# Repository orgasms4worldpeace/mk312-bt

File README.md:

# MK-312BT

DIY build of the **ErosTek ET-312B** e-stim power box, with Bluetooth (HC-05) or WiFi (ESP8266) wireless control. Boards, BOM, firmware, case, and the documentation needed to actually build one.

> ⚠️ **Safety.** This is a high-voltage device. Don't injure yourself. No warranty.

## How to build one

Work through the numbered directories in order. The full step-by-step walkthrough is in **[`build-guide.md`](build-guide.md)**.

| Step | Directory | What you do |
|------|-----------|-------------|
| 1 | [`1-order-boards/`](1-order-boards/) | Send the main-board + front-panel gerbers to JLCPCB |
| 2 | [`2-order-parts/`](2-order-parts/) | Import the BOM into Mouser. Pre-match MOSFETs by Vt — this prevents Error 20 |
| 3 | [`3-build-and-flash/`](3-build-and-flash/) | Solder, print the case, flash the ATmega16A |
| 4 | [`4-wireless/`](4-wireless/) | Pick **Bluetooth** (HC-05) or **WiFi** (ESP8266 — required for macOS / iOS) |
| 5 | [`5-software/`](5-software/) | Pick a control client (links to upstream projects — none bundled) |

If anything misbehaves, [`3-build-and-flash/troubleshooting/`](3-build-and-flash/troubleshooting/) has per-failure-code analyses and the archived metafetish.club forum threads.

## Speculative work in progress

See [`Roadmap.md`](Roadmap.md) for hardware/firmware ideas that haven't been verified end-to-end yet. Nothing in there is on the build path until it lands in the numbered directories.

## What this repo is (and isn't)

A 2026 reorganization of two dormant upstream projects into one build-journey monorepo. Scope: **boards, BOM, firmware, case, build instructions**. Control software stays upstream where it's maintained.

- Upstream for the box: [CrashOverride85/mk312-bt](https://github.com/CrashOverride85/mk312-bt) — boards, firmware, case
- Upstream for the WiFi adapter: [Rangarig/MK312WIFI](https://github.com/Rangarig/MK312WIFI) — pulled into [`4-wireless/wifi/`](4-wireless/wifi/) as a `git subtree`
- Control clients (`mk312-gui`, `ErosWeb`, `three-twelve-bee`, `restim`, etc.): index at [`5-software/`](5-software/) — install whichever from its own repo

This repo is **not** a fork claiming originality, **not** the "official" MK-312BT (there is no official), and **not** a maintained software hub. It's a curation effort with attribution preserved.

### Hardware lineage

```
ErosTek ET-312B               commercial e-stim box (early 2000s, still sold)
└─ metafetish/mk312-bt        community DIY clone, repo deleted ~Dec 2020
   └─ CrashOverride85/mk312-bt   preservation fork, current upstream
      └─ this repo                  2026 reorganization
```

v1.4 board files were DM'd to CrashOverride85 shortly after the metafetish repo was deleted, with no original Eagle source. The design has been built successfully by several people. v1.2 / v1.3 boards (with Eagle source) live in the upstream `CrashOverride85/mk312-bt` repo for anyone who wants to modify the design. Longer story in [`build-guide.md`](build-guide.md#provenance).

### Forum archive

The `metafetish.club` forum — where most community debugging knowledge accumulated — is now offline. Threads on building, Error 20, parts substitution, and firmware live as PDFs in [`3-build-and-flash/troubleshooting/`](3-build-and-flash/troubleshooting/).

## Credit

| Person / project | What they did |
|---|---|
| **CrashOverride85** | Preserved the metafetish repo; ongoing upstream for the box |
| **Rangarig** & **cLx** | MK312WIFI design, schematics, ESP firmware |
| **timduru** | Additional MK312WIFI code contributions |
| **kinkytofu** | [`buttshock-py`](https://github.com/kinkytofu/buttshock-py) — original ET-312 serial-protocol library, predecessor of every Python client |
| **clxjaguar** (cLx) | [`mk312-gui`](https://github.com/clxjaguar/mk312-gui) PyQt client, `mk312-raw-control` |
| **fenbyfluid** | [`three-twelve-bee`](https://github.com/fenbyfluid/three-twelve-bee) web client |
| **boyinsea** | [`ErosWeb`](https://github.com/boyinsea/ErosWeb) sub/dom remote-play client |
| **diglet48** | [`restim`](https://github.com/diglet48/restim) audio-input signal generator |
| **Rubberfate** | [`mk312com`](https://github.com/Rubberfate/mk312com) Python wrapper |
| **Carumbad** | Home Assistant + MQTT bridges |
| **The metafetish.club community** | Board iteration + decades of debug knowledge sitting in the archived threads |
| **ErosTek** | Designers of the ET-312B that this clones |

License: each upstream's original license carries over. New connective material in this repo (READMEs, `build-guide.md`, BOM tooling) is offered freely.

## Getting help

The active community lives in the `#boxes-pulse-based-diy` and `#312-chat` channels on [Joanne's E-Stim Community Discord](https://discord.gg/rY8C27S).

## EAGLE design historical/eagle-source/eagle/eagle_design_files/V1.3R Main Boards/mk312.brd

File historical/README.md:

# Historical artifacts

**Don't build from this folder.** Go back to [the root README](../README.md) and follow the numbered directories.

This folder preserves earlier MK-312BT board revisions and their source artifacts. Kept around because:

- Some builders still work from v1.2 / v1.3 boards they ordered years ago
- The Eagle source (`.brd` / `.sch`) lives here — v1.4 ships gerbers only, so to **modify** the design, start from the v1.3 source
- The build photos in [`images/`](images/) make a useful visual sanity check when assembling

## Contents

| | |
|--|--|
| [`boms/`](boms/) | Original Mouser BOM CSVs and the OpenOffice / Excel masters from the upstream repo |
| [`eagle-source/`](eagle-source/) | Eagle CAD source for v1.2 main board, v1.2 front panel, v1.3B and v1.3R main boards. Includes the Seeed Gerber generator CAM job |
| [`gerbers/`](gerbers/) | Output gerbers for v1.2 main board, v1.2 front panel, and v1.3 (revised) main board |
| [`images/`](images/) | Build photos for v1.0 and v1.2 |

## Note on v1.4

v1.4 is the current revision (see [`../1-order-boards/`](../1-order-boards/)). It changes only the **main board** — the v1.2 front panel design is still the right one to build.

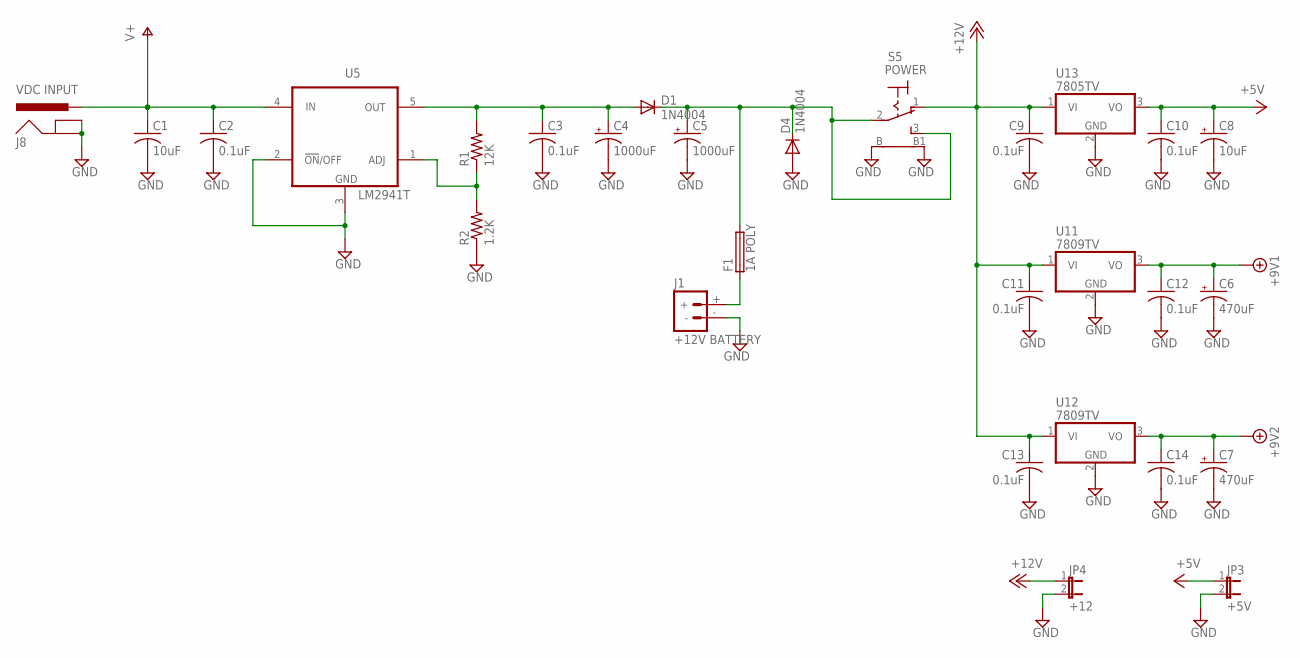
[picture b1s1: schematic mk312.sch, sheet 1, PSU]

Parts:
C1: 10uF; C050-024X044
C2, C3, C9, C10, C11, C12, C13, C14: 0.1uF; C025-024X044
C4, C5: 1000uF; E5-10,5
C6, C7: 470uF; E3,5-8
C8: 10uF; E2,5-7
D1, D4: 1N4004; DO41-10
F1: 1A POLY; LITTLEFUSE
J1: +12V BATTERY; DEANS
J8: VDC INPUT; POWER_JACK_SLOT
JP3: +5V; JP1
JP4: +12; JP1
R1: 12K; 0207/10
R2: 1.2K; 0207/10
S5: POWER; LPV-1
U5: LM2941T; TO220-5
U11, U12: 7809TV; TO220V
U13: 7805TV; TO220V

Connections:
+5V: C8.+, C10.1, JP3.1, U13.3 (VO); also elsewhere on the board
+8V: C6.+, C12.1, U11.3 (VO); also elsewhere on the board
+9V: C7.+, C14.1, U12.3 (VO); also elsewhere on the board
+12V: C9.1, C11.1, C13.1, JP4.1, S5.1 (O), U11.1 (VI), U12.1 (VI), U13.1 (VI); also elsewhere on the board
GND: C1.2, C2.2, C3.2, C4.-, C5.-, C6.-, C7.-, C8.-, C9.2, C10.2, C11.2, C12.2, C13.2, C14.2, D4.A, J1.-, J8.GND@1 (GNDBREAK), J8.GND@2 (GND), JP3.2, JP4.2, R2.1, S5.B, S5.B1, U5.2 (!ON!/OFF), U5.3 (GND), U11.2 (GND), U12.2 (GND), U13.2 (GND); also elsewhere on the board
unnamed: F1.1, J1.+
unnamed: R1.1, R2.2, U5.1 (ADJ)
unnamed: C3.1, C4.+, D1.A, R1.2, U5.5 (OUT)
unnamed: C5.+, D1.C, D4.C, F1.2, S5.2, S5.3 (S)
V+: C1.1, C2.1, J8.PWR, U5.4 (IN); also elsewhere on the board

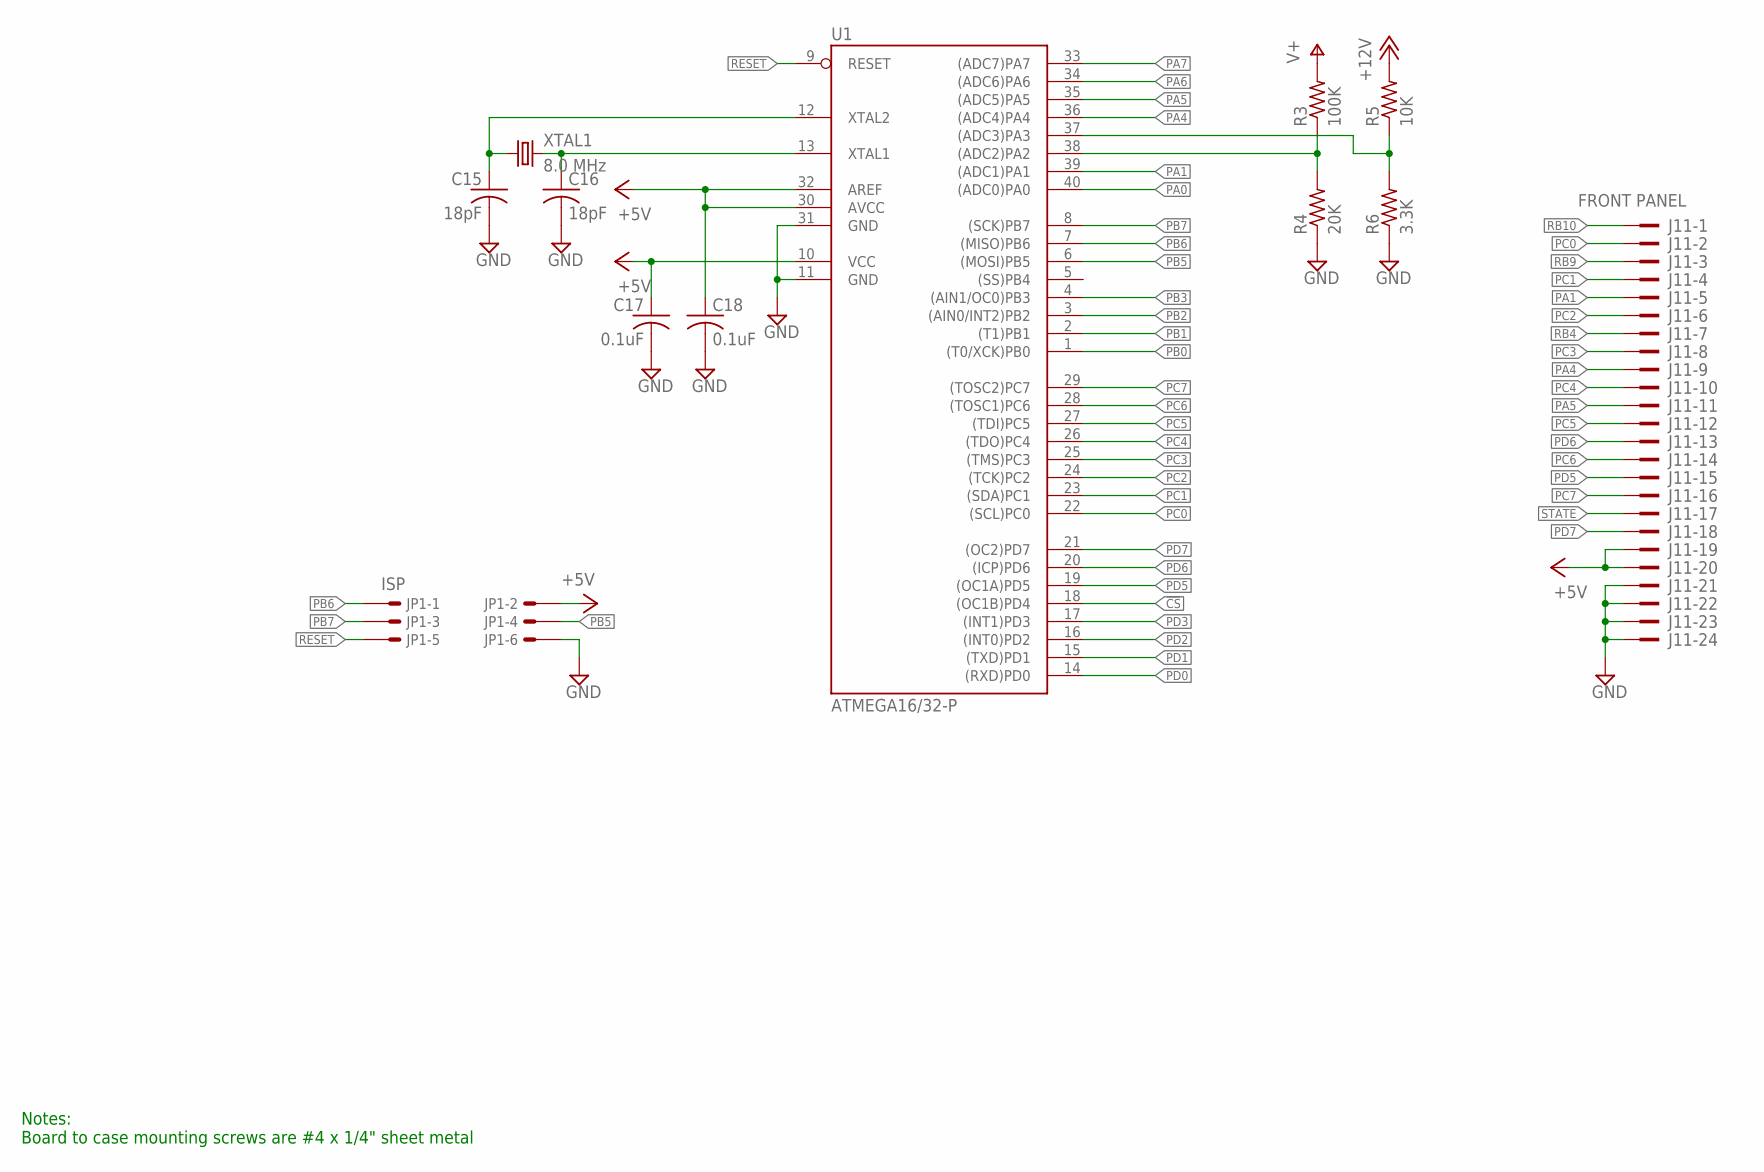
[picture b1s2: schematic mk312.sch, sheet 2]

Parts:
C15, C16: 18pF; C025-024X044
C17, C18: 0.1uF; C025-024X044
J11: FRONT PANEL; PAK100/2500-24
JP1: ISP; 057-006-1
R3: 100K; 0207/10
R4: 20K; 0207/10
R5: 10K; 0207/10
R6: 3.3K; 0207/10
U1: ATMEGA16/32-P; DIL40
XTAL1: 8.0 MHz; HC49/S

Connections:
!CS: U1.18 ((OC1B)PD4); also elsewhere on the board
+5V: C17.1, C18.1, J11.19, J11.20, JP1.2, U1.10 (VCC), U1.30 (AVCC), U1.32 (AREF); also elsewhere on the board
+12V: R5.2; also elsewhere on the board
GND: C15.2, C16.2, C17.2, C18.2, J11.21, J11.22, J11.23, J11.24, JP1.6, R4.1, R6.1, U1.11 (GND), U1.31 (GND); also elsewhere on the board
unnamed: R5.1, R6.2, U1.37 ((ADC3)PA3)
unnamed: R3.1, R4.2, U1.38 ((ADC2)PA2)
unnamed: C16.1, U1.13 (XTAL1), XTAL1.2
unnamed: C15.1, U1.12 (XTAL2), XTAL1.1
PA0: U1.40 ((ADC0)PA0); also elsewhere on the board
PA1: J11.5, U1.39 ((ADC1)PA1); also elsewhere on the board
PA4: J11.9, U1.36 ((ADC4)PA4)
PA5: J11.11, U1.35 ((ADC5)PA5)
PA6: U1.34 ((ADC6)PA6); also elsewhere on the board
PA7: U1.33 ((ADC7)PA7); also elsewhere on the board
PB0: U1.1 ((T0/XCK)PB0); also elsewhere on the board
PB1: U1.2 ((T1)PB1); also elsewhere on the board
PB2: U1.3 ((AIN0/INT2)PB2); also elsewhere on the board
PB3: U1.4 ((AIN1/OC0)PB3); also elsewhere on the board
PB5: JP1.4, U1.6 ((MOSI)PB5); also elsewhere on the board
PB6: JP1.1, U1.7 ((MISO)PB6)
PB7: JP1.3, U1.8 ((SCK)PB7); also elsewhere on the board
PC0: J11.2, U1.22 ((SCL)PC0); also elsewhere on the board
PC1: J11.4, U1.23 ((SDA)PC1); also elsewhere on the board
PC2: J11.6, U1.24 ((TCK)PC2); also elsewhere on the board
PC3: J11.8, U1.25 ((TMS)PC3); also elsewhere on the board
PC4: J11.10, U1.26 ((TDO)PC4); also elsewhere on the board
PC5: J11.12, U1.27 ((TDI)PC5); also elsewhere on the board
PC6: J11.14, U1.28 ((TOSC1)PC6); also elsewhere on the board
PC7: J11.16, U1.29 ((TOSC2)PC7); also elsewhere on the board
PD0: U1.14 ((RXD)PD0); also elsewhere on the board
PD1: U1.15 ((TXD)PD1); also elsewhere on the board
PD2: U1.16 ((INT0)PD2); also elsewhere on the board
PD3: U1.17 ((INT1)PD3); also elsewhere on the board
PD5: J11.15, U1.19 ((OC1A)PD5); also elsewhere on the board
PD6: J11.13, U1.20 ((ICP)PD6); also elsewhere on the board
PD7: J11.18, U1.21 ((OC2)PD7); also elsewhere on the board
RB4: J11.7; also elsewhere on the board
RB9: J11.3; also elsewhere on the board
RB10: J11.1; also elsewhere on the board
RESET: JP1.5, U1.9 (RESET)
STATE: J11.17; also elsewhere on the board
V+: R3.2; also elsewhere on the board

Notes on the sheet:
Notes: Board to case mounting screws are #4 x 1/4" sheet metal

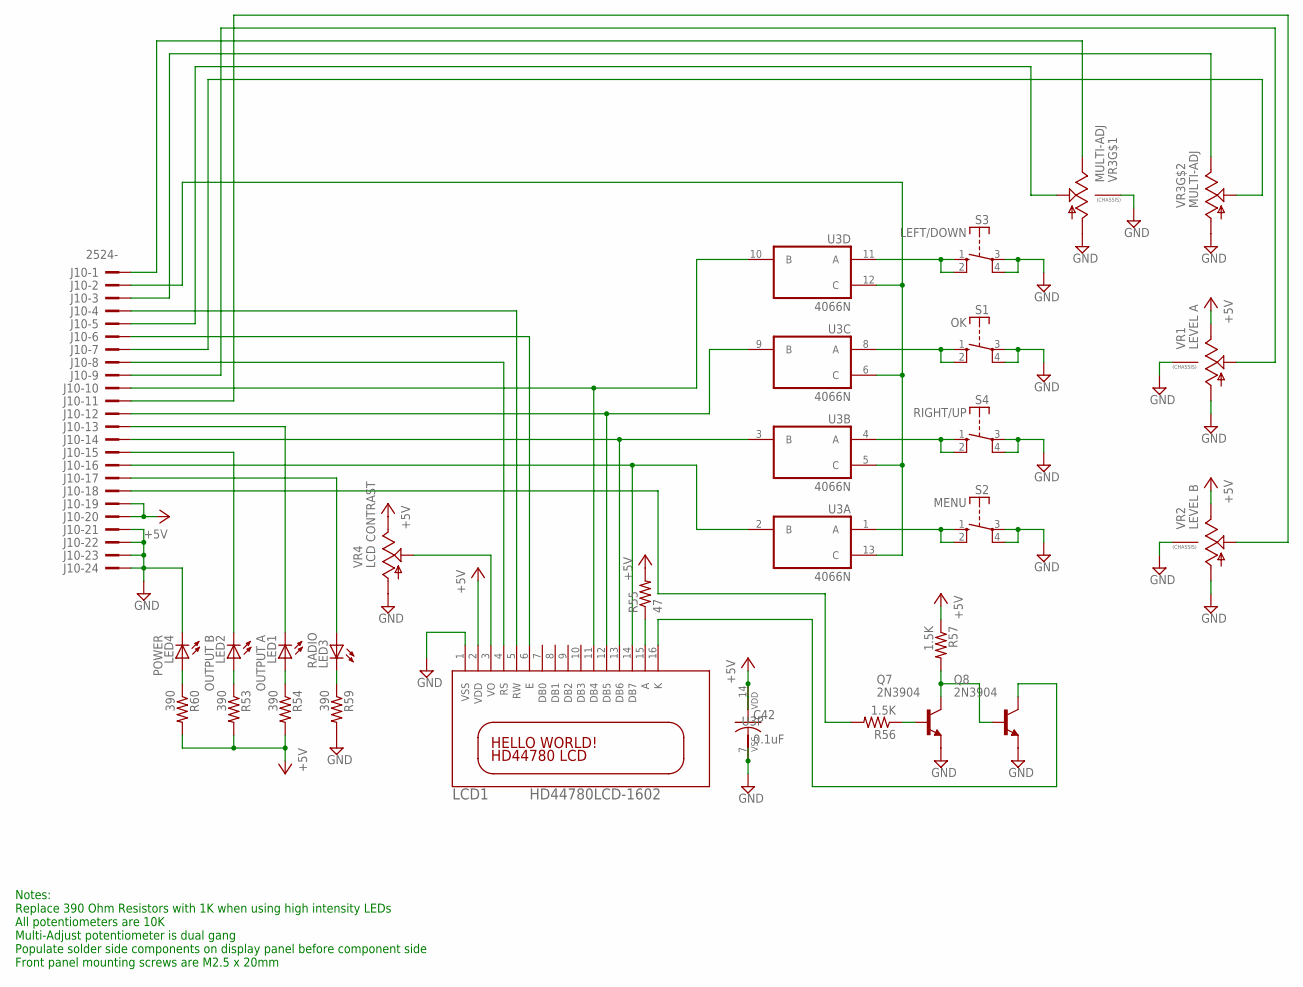
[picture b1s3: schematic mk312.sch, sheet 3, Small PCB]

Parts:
C42: 0.1uF; C025-024X044
J10: 2524-; PAK100/2500-24
LCD1: HD44780LCD-1602; LCD1602
LED1: OUTPUT A; LED5MM
LED2: OUTPUT B; LED5MM
LED3: RADIO; LED5MM
LED4: POWER; LED5MM
Q7, Q8: 2N3904; TO92
R53, R54, R59, R60: 390; 0207/10
R55: 47; 0207/10
R56, R57: 1.5K; 0207/10
S1: OK; DTE6K
S2: MENU; DTE6K
S3: LEFT/DOWN; DTE6K
S4: RIGHT/UP; DTE6K
U3: 4066N; DIL14
VR1: LEVEL A; 9MM_SNAP-IN_POT
VR2: LEVEL B; 9MM_SNAP-IN_POT
VR3: MULTI-ADJ; DUAL_9MM_SNAP-IN_POT
VR4: LCD CONTRAST; B25P

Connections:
+5V: C42.1, J10.19, J10.20, LCD1.2 (VDD), R53.2, R54.2, R55.2, R57.1, R60.2, U3.14 (VDD), VR1.3 (E), VR2.3 (E), VR4.E; also elsewhere on the board
GND: C42.2, J10.21, J10.22, J10.23, J10.24, LCD1.1 (VSS), LED4.K (C), Q7.3 (E), Q8.3 (E), R59.2, S1.3, S1.4, S2.3, S2.4, S3.3, S3.4, S4.3, S4.4, U3.7 (VSS), VR1.1 (A), VR1.CHASSIS2, VR2.1 (A), VR2.CHASSIS2, VR3.1 (A), VR3.1B (A), VR3.CHASSIS1, VR3.CHASSIS2, VR4.A; also elsewhere on the board
unnamed: J10.7, VR3.2B (S)
unnamed: S1.1 (S), S1.2 (S), U3.8 (A)
unnamed: S3.1 (S), S3.2 (S), U3.11 (A)
unnamed: S4.1 (S), S4.2 (S), U3.4 (A)
unnamed: J10.3, VR3.3B (E)
unnamed: J10.9, VR1.2 (S)
unnamed: J10.11, VR2.2 (S)
unnamed: J10.1, VR3.3 (E)
unnamed: J10.5, VR3.2 (S)
unnamed: LED2.A, R53.1
unnamed: LED1.A, R54.1
unnamed: LCD1.3 (VO), VR4.S
unnamed: LCD1.15 (A), R55.1
unnamed: LED3.K (C), R59.1
unnamed: S2.1 (S), S2.2 (S), U3.1 (A)
unnamed: LED4.A, R60.1
unnamed: Q7.2 (B), R56.1
unnamed: Q7.1 (C), Q8.2 (B), R57.2
unnamed: LCD1.16 (K), Q8.1 (C)
unnamed: J10.17, LED3.A
PC0: J10.2, U3.5 (C), U3.6 (C), U3.12 (C), U3.13 (C); also elsewhere on the board
PC1: J10.4, LCD1.5 (RW); also elsewhere on the board
PC2: J10.6, LCD1.6 (E); also elsewhere on the board
PC3: J10.8, LCD1.4 (RS); also elsewhere on the board
PC4: J10.10, LCD1.11 (DB4), U3.10 (B); also elsewhere on the board
PC5: J10.12, LCD1.12 (DB5), U3.9 (B); also elsewhere on the board
PC6: J10.14, LCD1.13 (DB6), U3.3 (B); also elsewhere on the board
PC7: J10.16, LCD1.14 (DB7), U3.2 (B); also elsewhere on the board
PD5: J10.15, LED2.K (C); also elsewhere on the board
PD6: J10.13, LED1.K (C); also elsewhere on the board
PD7: J10.18, R56.2; also elsewhere on the board

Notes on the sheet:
Notes: Replace 390 Ohm Resistors with 1K when using high intensity LEDs All potentiometers are 10K Multi-Adjust potentiometer is dual gang Populate solder side components on display panel before component side Front panel mounting screws are M2.5 x 20mm

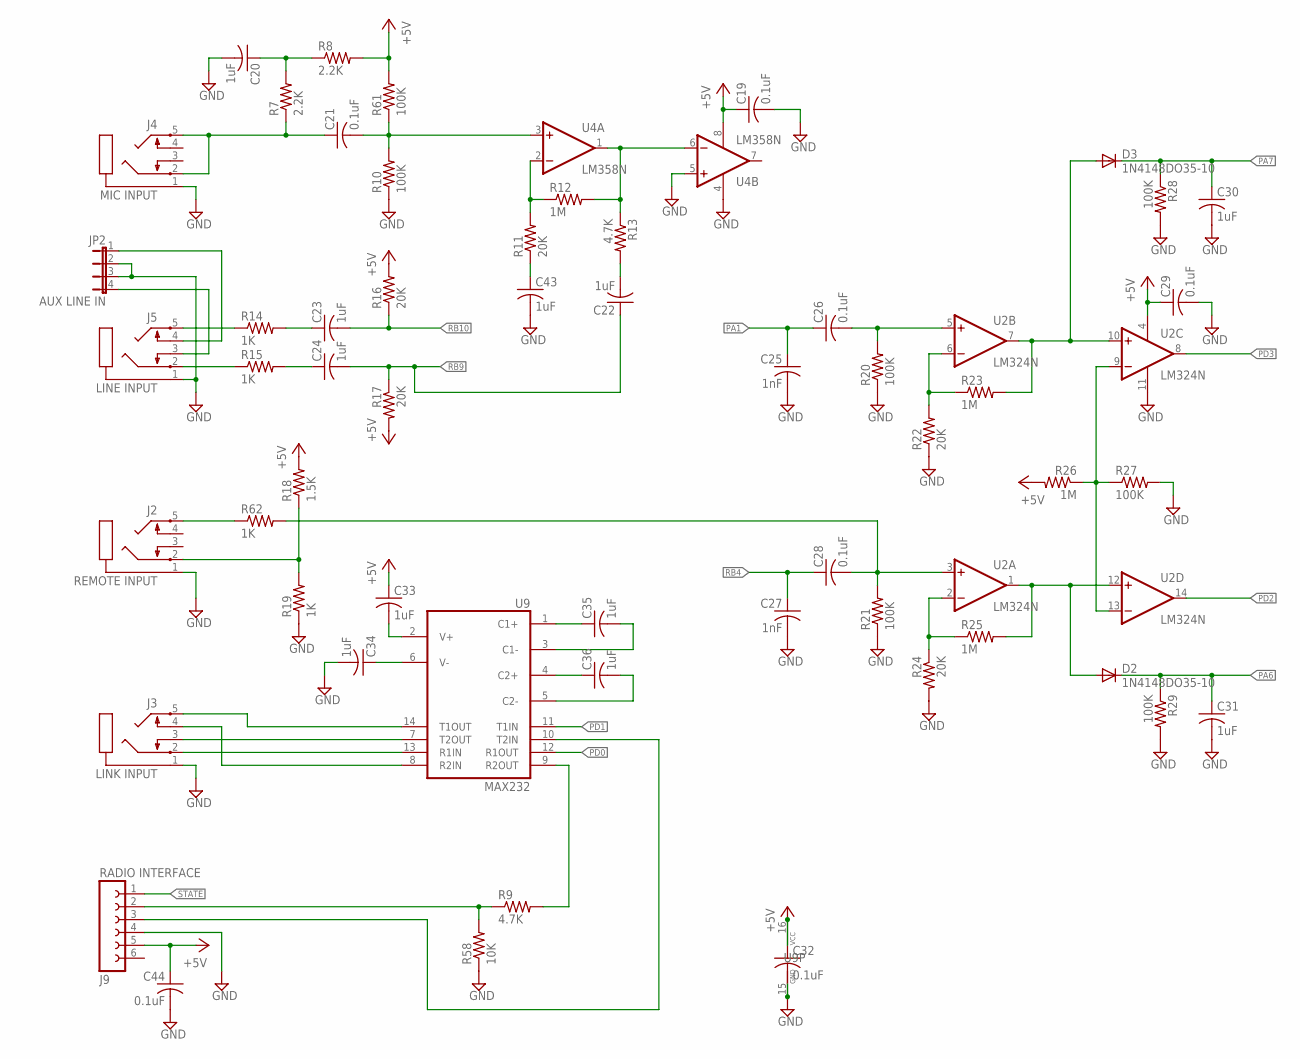
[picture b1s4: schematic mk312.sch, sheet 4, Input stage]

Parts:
C19, C21, C26, C28, C29, C32, C44: 0.1uF; C025-024X044
C20, C22, C23, C24, C30, C31, C33, C34, C35, C36, C43: 1uF; C025-024X044
C25, C27: 1nF; C025-024X044
D2, D3: 1N4148DO35-10; DO35-10
J2: REMOTE INPUT; STX3100
J3: LINK INPUT; STX3100
J4: MIC INPUT; STX3100
J5: LINE INPUT; STX3100
J9: RADIO INTERFACE; FE06
JP2: AUX LINE IN; JP4
R7, R8: 2.2K; 0207/10
R9, R13: 4.7K; 0207/10
R10, R20, R21, R27, R28, R29, R61: 100K; 0207/10
R11, R16, R17, R22, R24: 20K; 0207/10
R12, R23, R25, R26: 1M; 0207/10
R14, R15, R19, R62: 1K; 0207/10
R18: 1.5K; 0207/10
R58: 10K; 0207/10
U2: LM324N; DIL14
U4: LM358N; DIL08
U9: MAX232; DIL16

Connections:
+5V: C19.1, C29.1, C32.1, C33.1, C44.1, J9.5, R8.2, R16.2, R17.2, R18.2, R26.2, R61.2, U2.4 (V+), U4.8 (V+), U9.16 (VCC); also elsewhere on the board
GND: C19.2, C20.2, C25.2, C27.2, C29.2, C30.2, C31.2, C32.2, C34.2, C43.2, C44.2, J2.1, J3.1, J4.1, J5.1, J9.4, JP2.2, JP2.3, R10.1, R19.1, R20.1, R21.1, R22.1, R24.2, R27.2, R28.2, R29.2, R58.1, U2.11 (V-), U4.4 (V-), U4.5 (+IN), U9.15 (GND); also elsewhere on the board
unnamed: C28.2, R21.2, R62.2, U2.3 (+IN)
unnamed: R9.2, U9.9 (R2OUT)
unnamed: J3.5, U9.14 (T1OUT)
unnamed: J3.2, U9.13 (R1IN)
unnamed: C43.1, R11.1
unnamed: J2.5, R62.1
unnamed: C35.1, U9.1 (C1+)
unnamed: R24.1, R25.1, U2.2 (-IN)
unnamed: D2.A, R25.2, U2.1 (OUT), U2.12 (+IN)
unnamed: J5.2, R15.1
unnamed: J5.5, R14.1
unnamed: C23.1, R14.2
unnamed: J2.2, R18.1, R19.2
unnamed: J5.4, JP2.1
unnamed: R22.2, R23.1, U2.6 (-IN)
unnamed: C35.2, U9.3 (C1-)
unnamed: R26.1, R27.1, U2.9 (-IN), U2.13 (-IN)
unnamed: C26.2, R20.2, U2.5 (+IN)
unnamed: J5.3, JP2.4
unnamed: C24.1, R15.2
unnamed: C36.2, U9.5 (C2-)
unnamed: C36.1, U9.4 (C2+)
unnamed: J9.2, R9.1, R58.2
unnamed: D3.A, R23.2, U2.7 (OUT), U2.10 (+IN)
unnamed: C34.1, U9.6 (V-)
unnamed: C21.1, J4.2, J4.5, R7.1
unnamed: C20.1, R7.2, R8.1
unnamed: C21.2, R10.2, R61.1, U4.3 (+IN)
unnamed: R11.2, R12.1, U4.2 (-IN)
unnamed: R12.2, R13.1, U4.1 (OUT), U4.6 (-IN)
unnamed: C22.2, R13.2
unnamed: C33.2, U9.2 (V+)
unnamed: J3.4, U9.8 (R2IN)
unnamed: J3.3, U9.7 (T2OUT)
unnamed: J9.3, U9.10 (T2IN)
PA1: C25.1, C26.1; also elsewhere on the board
PA6: C31.1, D2.C, R29.1; also elsewhere on the board
PA7: C30.1, D3.C, R28.1; also elsewhere on the board
PD0: U9.12 (R1OUT); also elsewhere on the board
PD1: U9.11 (T1IN); also elsewhere on the board
PD2: U2.14 (OUT); also elsewhere on the board
PD3: U2.8 (OUT); also elsewhere on the board
RB4: C27.1, C28.1; also elsewhere on the board
RB9: C22.1, C24.2, R17.1; also elsewhere on the board
RB10: C23.2, R16.1; also elsewhere on the board
STATE: J9.1; also elsewhere on the board

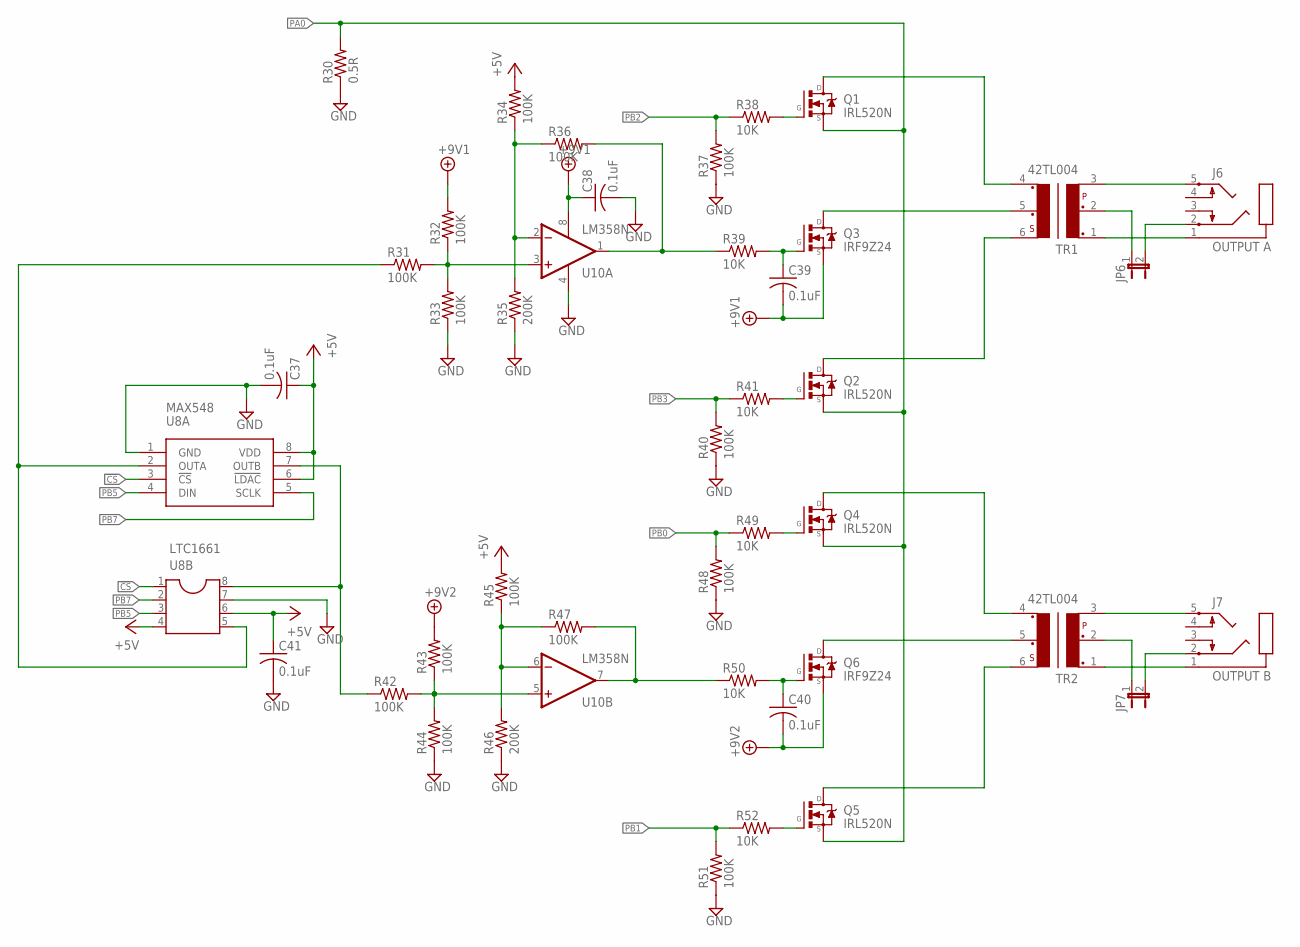
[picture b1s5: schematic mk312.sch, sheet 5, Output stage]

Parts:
C37, C38, C39, C40, C41: 0.1uF; C025-024X044
J6: OUTPUT A; STX3100
J7: OUTPUT B; STX3100
JP6, JP7: JP1E; JP1
Q1, Q2, Q4, Q5: IRL520N; TO220V
Q3, Q6: IRF9Z24; TO220V
R30: 0.5R; 0309/12
R31, R32, R33, R34, R36, R37, R40, R42, R43, R44, R45, R47, R48, R51: 100K; 0207/10
R35, R46: 200K; 0207/10
R38, R39, R41, R49, R50, R52: 10K; 0207/10
TR1, TR2: 42TL004; 42TL
U8A: MAX548; DIL08
U8B: LTC1661; SOCKET-08
U10: LM358N; DIL08

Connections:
!CS: U8A.3 (!CS), U8B.1; also elsewhere on the board
+5V: C37.1, C41.1, R34.2, R45.2, U8A.6 (!LDAC), U8A.8 (VDD), U8B.4, U8B.6; also elsewhere on the board
+8V: C38.1, C39.2, Q3.3 (S), R32.2, U10.8 (V+); also elsewhere on the board
+9V: C40.2, Q6.3 (S), R43.2; also elsewhere on the board
GND: C37.2, C38.2, C41.2, R30.1, R33.1, R35.1, R37.1, R40.1, R44.1, R46.1, R48.1, R51.1, U8A.1 (GND), U8B.7, U10.4 (V-); also elsewhere on the board
unnamed: Q3.2 (D), TR1.5
unnamed: Q6.2 (D), TR2.5
unnamed: JP7.1, TR2.2
unnamed: J6.1, TR1.1
unnamed: Q1.1 (G), R38.2
unnamed: Q2.1 (G), R41.2
unnamed: J7.2, JP7.2
unnamed: C39.1, Q3.1 (G), R39.2
unnamed: R31.2, R32.1, R33.2, U10.3 (+IN)
unnamed: Q4.1 (G), R49.2
unnamed: Q5.1 (G), R52.2
unnamed: J7.1, TR2.1
unnamed: C40.1, Q6.1 (G), R50.2
unnamed: R42.2, R43.1, R44.2, U10.5 (+IN)
unnamed: Q1.2 (D), TR1.4
unnamed: J6.5, TR1.3
unnamed: Q4.2 (D), TR2.4
unnamed: J7.5, TR2.3
unnamed: Q5.2 (D), TR2.6
unnamed: Q2.2 (D), TR1.6
unnamed: R34.1, R35.2, R36.1, U10.2 (-IN)
unnamed: R45.1, R46.2, R47.1, U10.6 (-IN)
unnamed: R31.1, U8A.2 (OUTA), U8B.5
unnamed: J6.2, JP6.2
unnamed: JP6.1, TR1.2
unnamed: R42.1, U8A.7 (OUTB), U8B.8
PA0: Q1.3 (S), Q2.3 (S), Q4.3 (S), Q5.3 (S), R30.2; also elsewhere on the board
PB0: R48.2, R49.1; also elsewhere on the board
PB1: R51.2, R52.1; also elsewhere on the board
PB2: R37.2, R38.1; also elsewhere on the board
PB3: R40.2, R41.1; also elsewhere on the board
PB5: U8A.4 (DIN), U8B.3; also elsewhere on the board
PB7: U8A.5 (SCLK), U8B.2; also elsewhere on the board
PFET_A: R36.2, R39.1, U10.1 (OUT)
PFET_B: R47.2, R50.1, U10.7 (OUT)

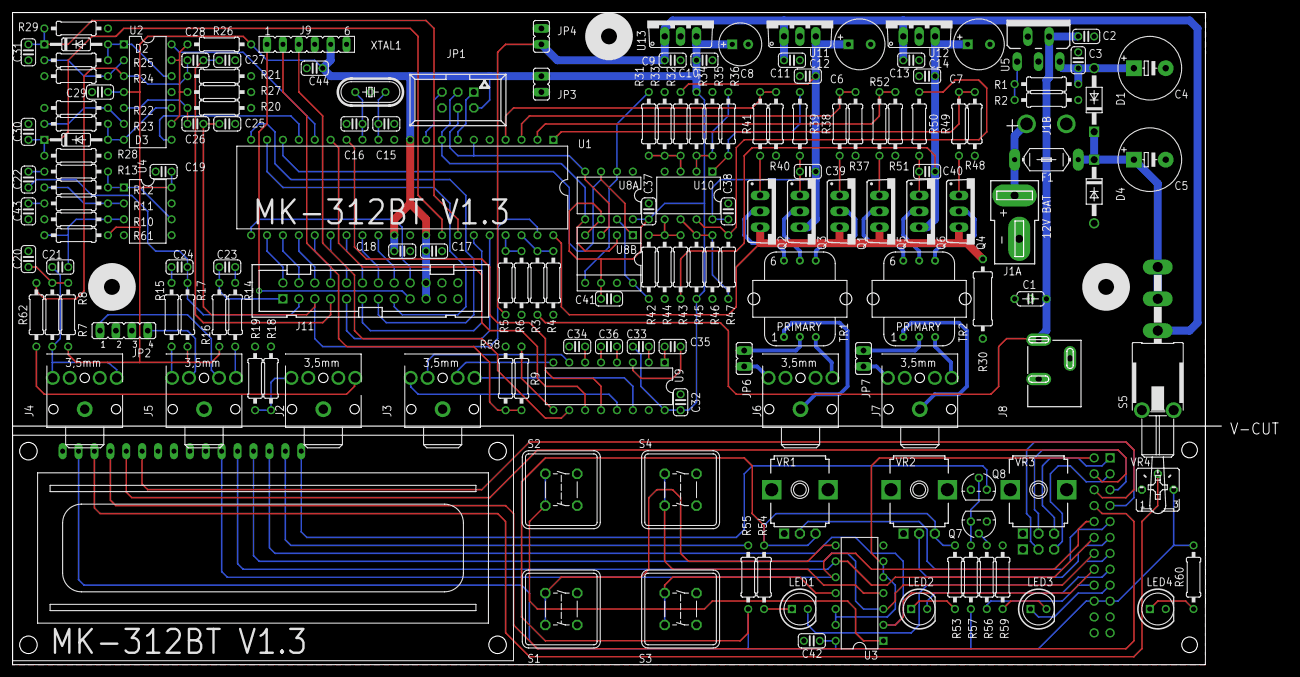
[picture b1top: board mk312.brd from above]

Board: 2 copper layers, 193.0 x 104.1 mm, 165 parts (1 on the bottom side), 131 nets.

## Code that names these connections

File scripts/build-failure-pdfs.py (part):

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    summary=(
        "Failure 20 is the post-boot output-stage self-test, and the most common build "
        "failure on first power-up. A single routine at <font face='Courier'>"
        "Function_0x1406</font> drives PB2+PB3 (channel A) and then PB0+PB1 (channel B) "
        "while monitoring ADC0 (R30 current sense). On each pass it ramps the DAC down "
        "from a low-power seed and looks for the R30 current to settle within bounds. "
        "If either channel can't deliver current, or the current runs away, F20 fires. "
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             "    1410:  ldi  r26, 100         ; DAC seed = 100 (≈OUTA 4.38V)\n"
             "    143a:  cp   r16, 0\n"
             "    143c:  brne 0x1444           ; channel B branch\n"
             "    143e:  ldi  r26, 0x0c        ; PORTB = 0b00001100 (PB2+PB3 = q5+q6)\n"
             "    1440:  out  PORTB, r26       ; ← drives channel A FETs\n"
             "    1444:  ldi  r26, 0x03        ; PORTB = 0b00000011 (PB0+PB1 = q7+q8)\n"
             "    1446:  out  PORTB, r26       ; ← drives channel B FETs\n"
             "    1448-1452:                   ; pulse-width delay\n"
             "    1456:  out  PORTB, 0         ; gates OFF\n"
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    title="Wall-adapter voltage too high (ADC2 ≥ 146 → U+ ≥ ~17.1 V)",
    summary=(
        "Failure 21 is a boot-time voltage check that runs <i>before</i> F20. The "
        "firmware reads ADC2 (PA2, fed by the R3 100kΩ / R4 20kΩ divider from raw input "
        "U+) and trips F21 if the reading is ≥ 146. Through that divider, ADC2=146 "
        "corresponds to U+ ≈ 17.1 V at J8. F21 means the wall adapter is over-spec, OR "
        "the ADC reference / divider / ribbon is reading garbage. The forum lore that "
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             "    16e0:  brcs 0x16e6           ;   <146 → continue\n"
             "    16e2:  ldi  r26, 0x15        ; ← loads code 21\n"
             "    16e4:  rjmp 0x1676           ; ← FAILURE 21"),
            "Voltage-divider math: ADC threshold 146/255 × 5.00 V = 2.86 V at PA2. "
            "Divider R3=100kΩ / R4=20kΩ gives PA2 = U+ × 20/(100+20) = U+/6. "
            "Threshold U+ = 2.86 × 6 = <b>~17.1 V</b>."
        ]),
        ("BOM tension", [
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            "2. <b>ADC reference issue</b> — AVCC (pin 30) or AREF (pin 32) noisy or "
            "mis-wired, causing ADC2 to read high.",
            "3. <b>Divider component fault</b> — R3 (100kΩ) open or R4 (20kΩ) shorted "
            "would push PA2 to the supply rail.",
            "4. <b>Ribbon-induced fault</b> — front-panel ribbon induced noise on PA2 "
            "during boot.",
            "5. <b>LCD POR timing</b> — the user's own boards (this repo) reproduced an "
            "intermittent F21 traced to LCD initialization timing rather than actual "
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            "ADC / divider / ribbon investigation per "
            "<font face='Courier'>failure-21-analysis.md</font> §3-§4.",
            "3. Measure resistance R3 → 100 kΩ ± 1%, R4 → 20 kΩ ± 1%. Check D5 (1N4148 "
            "clamp at PA2) is not shorted.",
            "4. Reseat the front-panel ribbon. If F21 was intermittent, this often "
            "clears it.",
        ]),
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
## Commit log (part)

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2026-04-26 Reorganize: stage v1.4/ + old/ structure
    - Remove pre-v1.4 sprawl (Eagle source, BOMs, case, gerbers) at root
    - Move v1.2/v1.3 artifacts under old/ (renamed to historical/ in next commit)
    - Stage new v1.4/ tree: bluetooth, bom, case, firmware, forum_docs,
    gerbers, schematics, tutorials, plus updated Mouser BOM with Amazon links
    - Add .gitignore for .DS_Store, Eagle lock/backup files
    - Drop duplicate v1.4/MK-312BT-BOM-Mouser.csv (kept v1.4/bom/ copy)
2026-04-26 Reorganize into journey-ordered tree
    Top level reflects the build path:
    1-order-boards/ gerbers, schematics, board layout, v1.4 release notes
    2-order-parts/ BOM-full.csv (master), BOM-mouser-cart.csv, BOM-with-amazon.xlsx
    3-build-and-flash/ firmware, case (3D print), tutorials
    4-wireless/ bluetooth/ (HC-05 init + setup guide); wifi/ added next commit
    docs/troubleshooting/ metafetish forum PDFs (Failure 20, transformer Q,
2026-04-26 Squashed '4-wireless/wifi/' content from commit 6a1ef85
    git-subtree-dir: 4-wireless/wifi
    git-subtree-split: 6a1ef85085a63a67bb5a7b60db7917319ead7d4f
2026-04-26 Rewrite README, add per-section build guides, surface front panel
    Root README is now a journey-oriented entry point: short overview,
    1→2→3→4 table, links to per-section READMEs, link to the
    comprehensive build guide. Replaces the stale Jan 2021 / V1.3-era
    README.
    Per-section READMEs added at each step (1-order-boards,
    2-order-parts, 3-build-and-flash, 4-wireless, docs/troubleshooting,
2026-04-27 Squashed '5-software/mk312-gui/' content from commit 96cf40b
    git-subtree-dir: 5-software/mk312-gui
    git-subtree-split: 96cf40ba58547e2bcd1925ae055b41907b1aad91
2026-04-27 Add 5-software/ step: mk312-gui (PyQt) as subtree, plus client index
    Pulls clxjaguar/mk312-gui into 5-software/mk312-gui/ via git subtree
    (--squash from main). cLx co-authored MK312WIFI, so the GUI speaks
    its protocol natively (UDP discovery on 8842, TCP control on 8843).
    Also handles the legacy ET-312 RS232 link mode and ships an mpv LUA
    script for video-subtitle-driven control.
    5-software/README.md indexes other Python clients (mk312-raw-control,
2026-04-27 Add JLCPCB-ready package for MK312 WiFi adapter PCB (SMT-only path)
    Drop-in upload bundle at 4-wireless/wifi-jlcpcb/ — gerbers + BOM + CPL
    prebuilt for JLCPCB ordering with SMT-only assembly. JLC pre-mounts
    the one SMD part (U1, AMS1117-3.3 in SOT-223, LCSC C6186); the 6
    through-hole parts (C1, C2, Q1, SW1, J1, J2) are user-soldered.
    Cost target: ~$20-25 for 5 boards. Full PCBA-with-THT runs $65-100+
    because of THT setup fees (~$30-50 one-time + extended-part loaded
2026-04-27 Reorganize: consolidate WiFi adapter content, move clients to 5-software, add CLAUDE.md
    Several rounds of in-progress reorganization across sessions left the
    tree messy. This commit consolidates the layout so each thing lives
    where it logically belongs:
    WiFi subtree internal layout (4-wireless/wifi/):
    - MK312Wifi/ (briefly application/) → firmware/ — matches naming of
    3-build-and-flash/firmware/ for the AVR side; both are "firmware
2026-04-28 Fix BOM: 7 resistor errors, 4 cap groupings, 2 missing diodes (v1.4 schematic verified)
    Cross-checked every R/C/D entry against the v1.4 schematic pages 1-5.
    Resistor value corrections:
    - R7, R8: were grouped at 4.7K, schematic shows 2.2K (mic input
    filter pair) — split off into new "R7,R8 RES 2.2K" line
    - R9: stays at 4.7K, now grouped with R13
    - R13: was a separate line at 47K, schematic shows 4.7K (mic preamp
2026-04-28 Fix R55: 47R -> 100R to match v1.4 schematic
    The BOM had R55 at 47 ohm, schematic page 3 shows 100 ohm in series
    with the LCD backlight LED, and v1.4 release notes recommend
    100-220 ohm for "single LED in New Haven displays." This build uses
    the BOM-listed Newhaven NHD-0216K1Z, so 100 ohm is the right value.
    Mouser part 660-MF1/4DCT52R1000F (MF1/4DCT52R1000F) — the same part
    that was previously listed as "LED Brightness Opt. 1" before that
2026-04-28 LED1-4: split single LED line into per-color Kingbright entries
    Color assignment per user spec:
    - LED1 (OUTPUT A) = orange Kingbright WP7113OD
    - LED2 (OUTPUT B) = orange Kingbright WP7113OD
    - LED3 (RADIO) = red Kingbright WP7113ID
    - LED4 (POWER) = green Kingbright WP7113GD
    All standard-brightness diffused 5mm leaded — picked specifically so
2026-04-28 BOM: add F1 polyfuse, drop R30 0.5R alternate, sync cart CSV
    Schematic page 1 calls out F1 as a 1A POLY between the battery/fuse
    header and the power switch — protects against shorts. Was missing
    from BOM entirely. Added as Bourns MF-R110 (1.1A hold / 2.2A trip
    radial polyfuse, 30V) at Mouser 652-MF-R110.
    Removed the R30 0.5R 1/2W alternate line — this build uses 0.27R
    (matches the 1000uF C6/C7 high-output config). Single R30 line now.
2026-04-28 BOM: add WiFi adapter section with SMD-vs-THT split explanation
    The BOM previously had only a one-line "Wifi Module (see their parts
    list)" entry pointing at upstream — opaque for someone deciding
    between BT and WiFi. Replaced with a structured section:
    - Restructured wireless choice as "pick ONE: bluetooth OR wifi"
    - Added macOS caveat on HC-05 (Classic SPP deprecated -> use WiFi)
    - Full WiFi adapter parts list with the JLCPCB SMT-only build path
2026-04-28 5-software: drop bundled mk312-gui + dotnet-client, link upstreams instead
    User decision (2026-04): repo scope is hardware/firmware/PCB, not
    maintaining forks of other people's control software. Removed both
    bundled subtrees:
    - 5-software/mk312-gui/ (was clxjaguar/mk312-gui subtree)
    - 5-software/dotnet-client/ (was relocated from MK312WIFI subtree)
    Replaced with a links-only README at 5-software/README.md indexing
2026-04-28 DotNetClient back inside wifi/ package; cart CSV Mouser-orderable only
    Per user feedback: the .NET reference client is part of the
    upstream MK312WIFI package (cLx shipped it alongside the firmware
    and PCB). Restored to its original location at
    4-wireless/wifi/DotNetClient/ matching upstream layout.
    Removing it earlier and bouncing it through 5-software/ was a
    unilateral reorg decision — undone now. The wifi subtree directory
2026-04-28 Add original debug docs: board-test-methodology PDF + F21 disassembly analysis
    The metafetish.club forum (the canonical MK-312BT troubleshooting venue) is
    offline and its mirrored PDFs only get you so far. This commit adds two pieces
    of original, evidence-based debug documentation written from disassembling the
    firmware and walking the v1.4 schematic + BASCOM HC-05 init source:
    - docs/troubleshooting/debug-notes/board-test-methodology.pdf
    9-page bench procedure for the "LCD shows solid blocks, no text" symptom

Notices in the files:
parts and their libraries:
SparkFun-Connectors: Licensing: Creative Commons ShareAlike 4.0 International - https://creativecommons.org/licenses/by-sa/4.0
national-semi: Copyright (C) 2008, Bob Starr
